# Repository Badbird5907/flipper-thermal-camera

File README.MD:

# Flipper Zero Thermal Camera

This is a thermal camera module for the Flipper Zero!

It uses the MLX90640 thermal sensor, with a *whopping* resolution of 32x24, and a suite of other auxiliary sensors, including:
- VEML7700 Light Sensor
- ICM-20948 IMU
- SHT31 Temperature & Humidity Sensor

All 4 sensors communicate to the flipper via it's I2C bus.

### The PCB
This is a simple two-layer PCB that mounts the MLX90640 and VEML7700 sensors in the front, and the ICM-20948 and SHT31 on the back.
It uses two 90-degree header pins to connect to the flipper zero's GPIO.

**Why no case?** Most flipper PCB mods don't use a case to show off the PCB. I think it especially goes better with my flipper as it has a clear case mod.

### The App

I have the app bootstrapped in [flipper-app](/flipper-app). It's not complete yet as I cannot test without the PCB.

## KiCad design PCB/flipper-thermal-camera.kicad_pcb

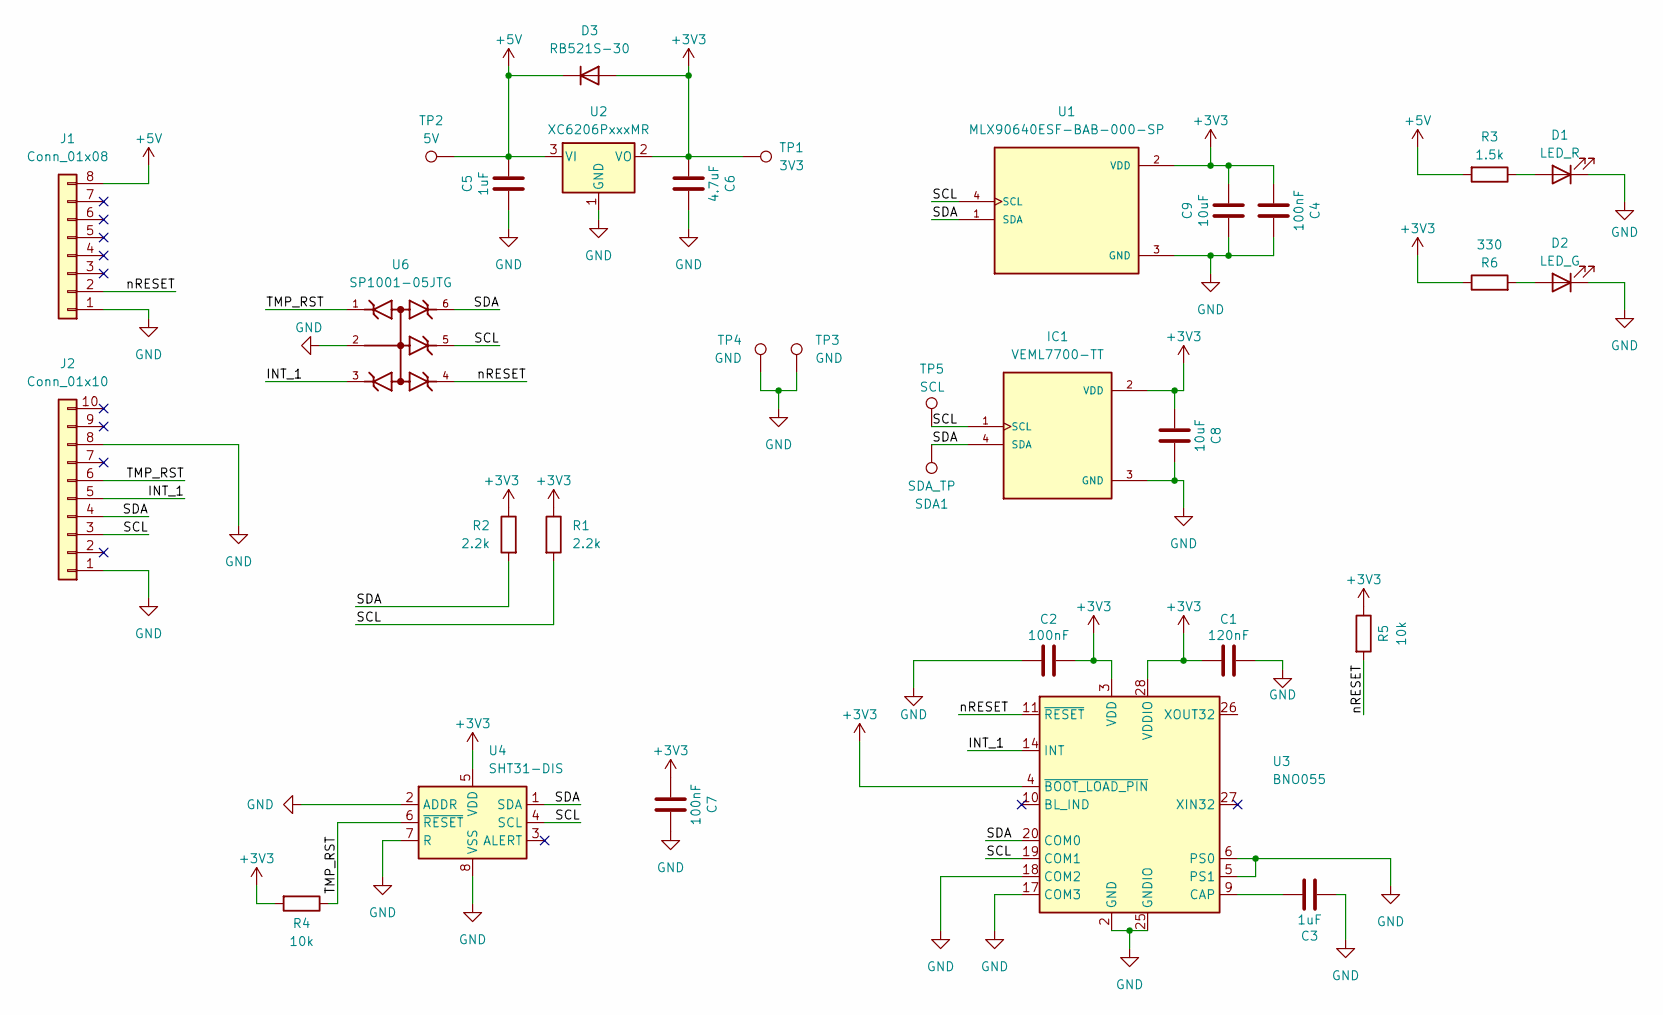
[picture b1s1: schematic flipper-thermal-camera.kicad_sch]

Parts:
C1: 120nF; C_0805_2012Metric
C2, C4, C7: 100nF; C_0805_2012Metric
C3, C5: 1uF; C_0805_2012Metric
C6: 4.7uF; C_0805_2012Metric
C8, C9: 10uF; C_0805_2012Metric
D1: LED_R; LED_0805_2012Metric
D2: LED_G; LED_0805_2012Metric
D3: RB521S-30; D_SOD-523; LCSC C727120
IC1: VEML7700-TT; XDCR_VEML7700-TT; Manufacturer_Part_Number VEML7700-TT; Mouser Part Number 78-VEML7700-TT
J1: Conn_01x08; PinHeader_1x08_P2.54mm_Horizontal
J2: Conn_01x10; PinHeader_1x10_P2.54mm_Horizontal
R1, R2: 2.2k; R_0805_2012Metric
R3: 1.5k; R_0805_2012Metric
R4, R5: 10k; R_0805_2012Metric
R6: 330; R_0805_2012Metric
SDA1: SDA_TP; TestPoint_Pad_D2.0mm
TP1: 3V3; TestPoint_Pad_D2.0mm
TP2: 5V; TestPoint_Pad_D2.0mm
TP3, TP4: GND; TestPoint_Pad_D2.0mm
TP5: SCL; TestPoint_Pad_D2.0mm
U1: MLX90640ESF-BAB-000-SP; TO292P945H1165-4; PARTREV 11
U2: XC6206PxxxMR; SOT-23-3
U3: BNO055; LGA-28_5.2x3.8mm_P0.5mm
U4: SHT31-DIS; Sensirion_DFN-8-1EP_2.5x2.5mm_P0.5mm_EP1.1x1.7mm
U6: SP1001-05JTG; SOP65P220X110-6N; PARTREV GD

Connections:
+3V3: C1.1, C2.2, C4.1, C6.2, C7.1, C8.1, C9.1, D3.2 (A), IC1.2 (VDD), R1.1, R2.1, R4.2, R5.1, R6.1, TP1.1 (1_1), U1.2 (VDD), U2.2 (VO), U3.3 (VDD), U3.4 (~BOOT_LOAD_PIN), U3.28 (VDDIO), U4.5 (VDD)
+5V: C5.2, D3.1 (K), J1.8, R3.2, TP2.1 (1_1), U2.3 (VI)
/INT_1: J2.5, U3.14 (INT), U6.3
/SCL: IC1.1 (SCL), J2.3, R1.2, TP5.1 (1_1), U1.4 (SCL), U3.19 (COM1), U4.4 (SCL), U6.5
/SDA: IC1.4 (SDA), J2.4, R2.2, SDA1.1 (1_1), U1.1 (SDA), U3.20 (COM0), U4.1 (SDA), U6.6
/TMP_RST: J2.6, R4.1, U4.6 (~RESET), U6.1
/nRESET: J1.2, R5.2, U3.11 (~RESET), U6.4
GND: C1.2, C2.1, C3.1, C4.2, C5.1, C6.1, C7.2, C8.2, C9.2, D1.1 (K), D2.1 (K), IC1.3 (GND), J1.1, J2.1, J2.8, TP3.1 (1_1), TP4.1 (1_1), U1.3 (GND), U2.1 (GND), U3.2 (GND), U3.5 (PS1), U3.6 (PS0), U3.17 (COM3), U3.18 (COM2), U3.25 (GNDIO), U4.2 (ADDR), U4.7 (R), U4.8 (VSS), U4.9 (VSS), U6.2
unnamed: D1.2 (A), R3.1
unnamed: D2.2 (A), R6.2
unnamed: C3.2, U3.9 (CAP)

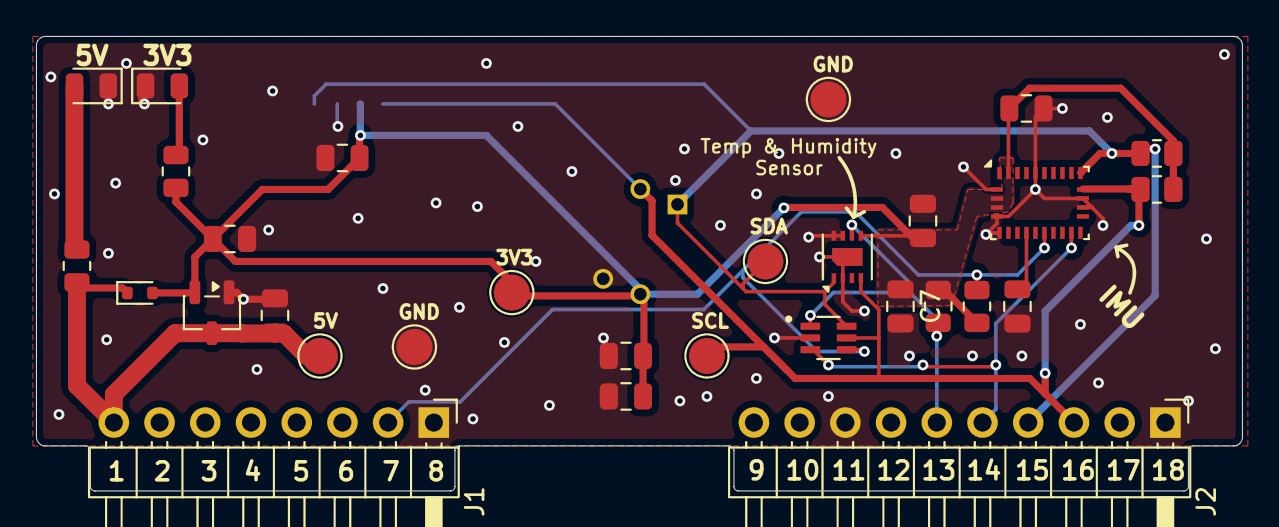
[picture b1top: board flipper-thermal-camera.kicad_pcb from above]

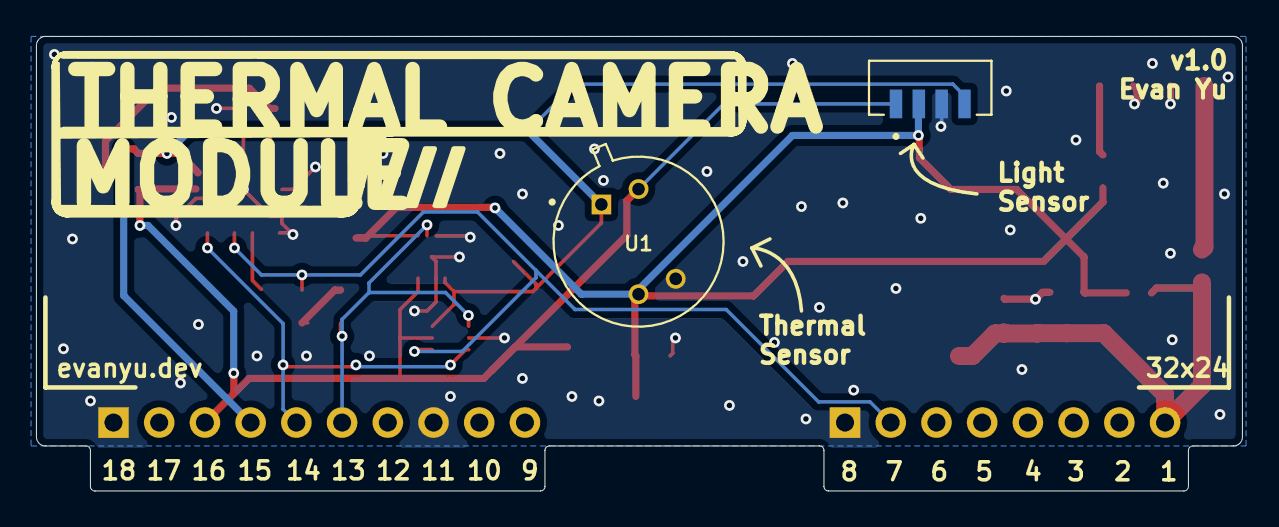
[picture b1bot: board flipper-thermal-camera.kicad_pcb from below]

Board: 2 copper layers, 67.0 x 25.2 mm, 32 parts (2 on the bottom side), 11 nets.

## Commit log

2026-05-10 add IMU, temp sensor, and light sensor + capacitors
2026-05-10 finish schematic
2026-05-10 finish routing pcb
2026-05-10 add testpoints
2026-05-10 source parts
2026-05-18 add bom
2026-05-19 add flipper app code
2026-05-19 add readme
2026-05-19 Add image render to README
2026-05-19 Enhance README with sensor and PCB information
    Added details about the thermal camera's sensors and PCB design.
2026-05-19 some temp testing code that probably won't work
2026-05-19 Add schematic image to README
    Added schematic image to README.
2026-05-24 update silkscreen & stuff
2026-05-24 add arrows and stuff
2026-05-24 fix arrow widths
2026-06-07 switch IMU and add more capacitors and diodes
2026-06-07 fix up wiring
2026-06-08 source from digikey
2026-06-25 get code working
2026-06-26 more fw stuff
